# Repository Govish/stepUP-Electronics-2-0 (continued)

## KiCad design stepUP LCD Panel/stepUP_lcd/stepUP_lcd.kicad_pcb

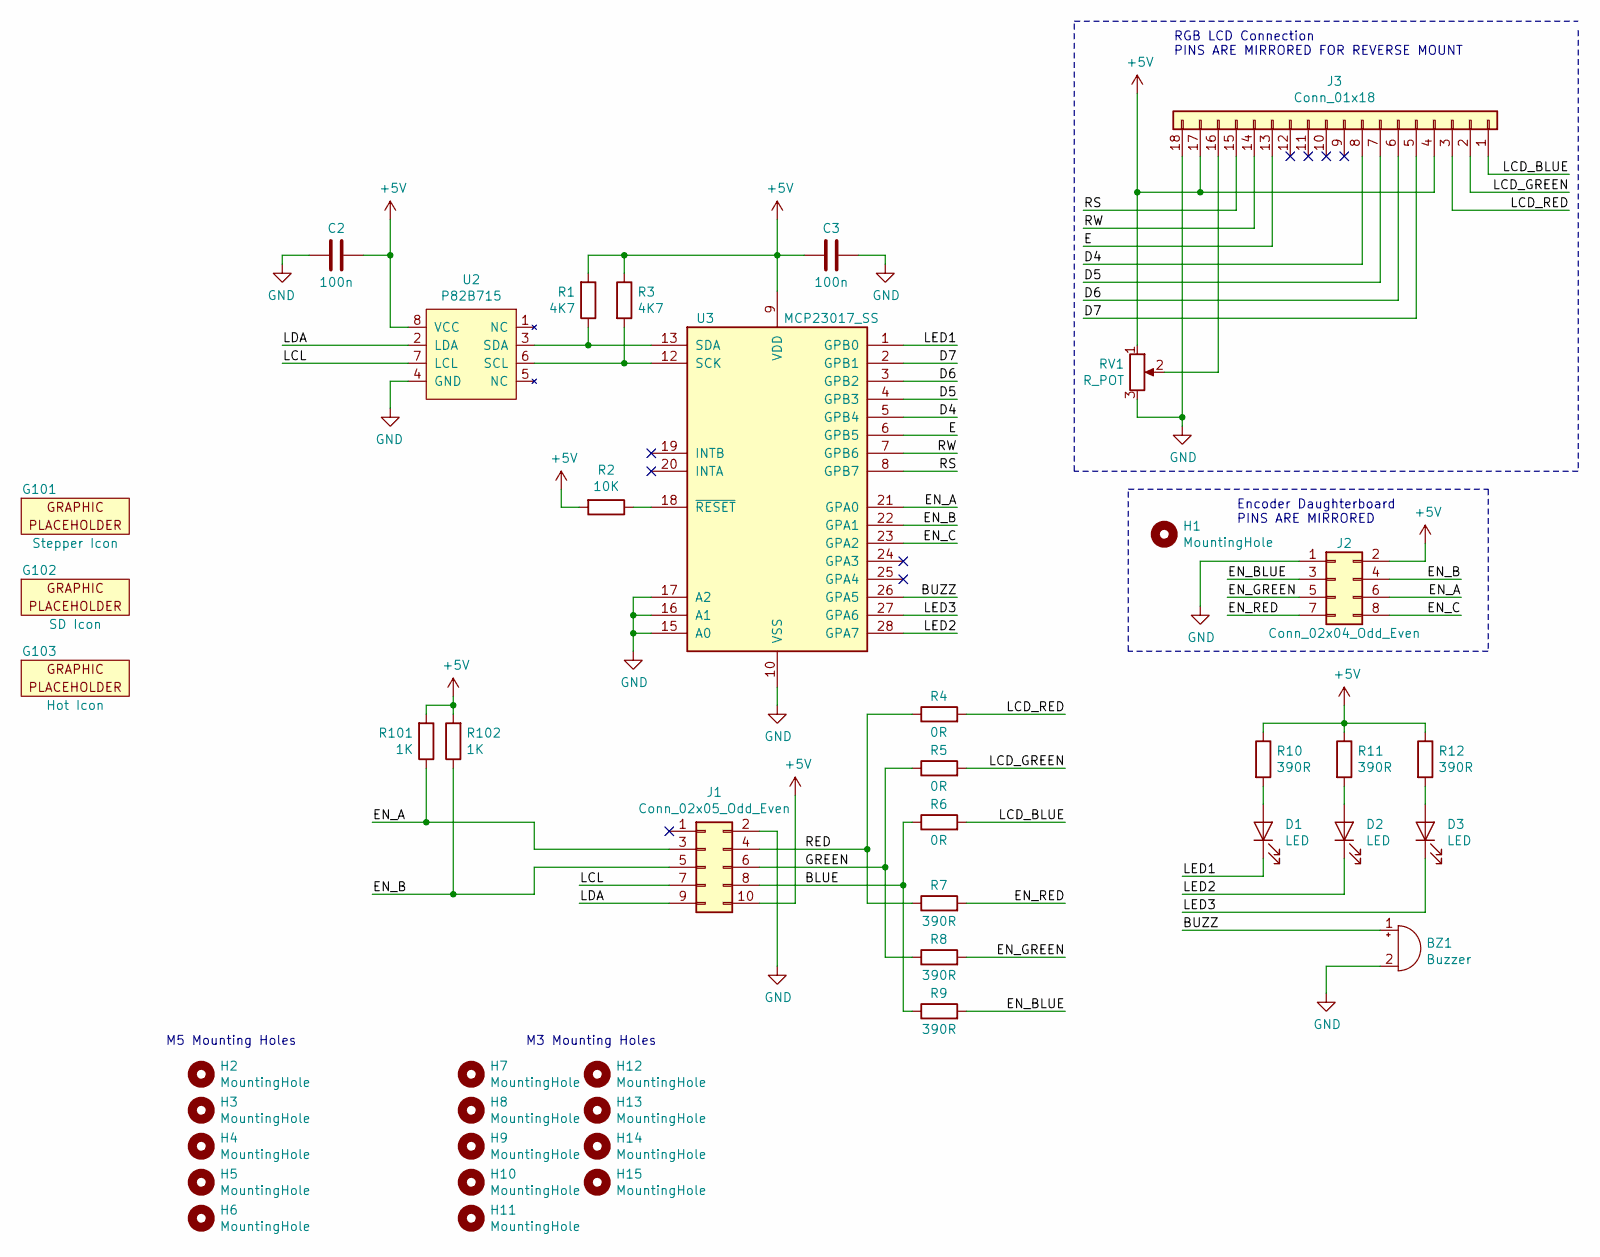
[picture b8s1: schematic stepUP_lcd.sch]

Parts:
BZ1: Buzzer; Buzzer_CUI_CPT9019S
C2, C3: 100n; C_0603_1608Metric_Pad1.05x0.95mm_HandSolder
D1, D2, D3: LED; LED_1206ReverseMount
G101: Stepper Icon; Icon_Stepper
G102: SD Icon; Icon_SD
G103: Hot Icon; Icon_Temp
H1: MountingHole; RGB_Encoder_Hole
H2, H3, H4, H5, H6: MountingHole; MountingHole_5.3mm_M5_Pad
H7, H8, H9, H10, H11, H12, H13, H14, H15: MountingHole; MountingHole_3.2mm_M3_Pad
J1: Conn_02x05_Odd_Even; PinHeader_2x05_P2.54mm_Shrouded
J2: Conn_02x04_Odd_Even; PinHeader_2x04_P2.54mm_Vertical_SMD
J3: Conn_01x18; PinHeader_1x18_P2.54mm_Vertical_SMD_Pin1Left
R1, R3: 4K7; R_0603_1608Metric_Pad1.05x0.95mm_HandSolder
R2: 10K; R_0603_1608Metric_Pad1.05x0.95mm_HandSolder
R4, R5, R6: 0R; R_0603_1608Metric_Pad1.05x0.95mm_HandSolder
R7, R8, R9, R10, R11, R12: 390R; R_0603_1608Metric_Pad1.05x0.95mm_HandSolder
R101, R102: 1K; R_0603_1608Metric_Pad1.05x0.95mm_HandSolder
RV1: R_POT; Potentiometer_Vishay_TS53YJ
U2: P82B715; SOIC-8_3.9x4.9mm_P1.27mm
U3: MCP23017_SS; SSOP-28_5.3x10.2mm_P0.65mm

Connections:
+5V: C2.2, C3.2, J1.10, J2.2, J3.4, J3.17, R1.2, R2.2, R3.1, R10.1, R11.1, R12.1, R101.2, R102.2, RV1.1, U2.8 (VCC), U3.9 (VDD)
/BLUE: J1.8, R6.1, R9.1
/BUZZ: BZ1.1 (-), U3.26 (GPA5)
/D4: J3.8, U3.5 (GPB4)
/D5: J3.7, U3.4 (GPB3)
/D6: J3.6, U3.3 (GPB2)
/D7: J3.5, U3.2 (GPB1)
/E: J3.13, U3.6 (GPB5)
/EN_A: J1.3, J2.6, R101.1, U3.21 (GPA0)
/EN_B: J1.5, J2.4, R102.1, U3.22 (GPA1)
/EN_BLUE: J2.3, R9.2
/EN_C: J2.8, U3.23 (GPA2)
/EN_GREEN: J2.5, R8.2
/EN_RED: J2.7, R7.2
/GREEN: J1.6, R5.1, R8.1
/LCD_BLUE: J3.1, R6.2
/LCD_GREEN: J3.2, R5.2
/LCD_RED: J3.3, R4.2
/LCL: J1.7, U2.7 (LCL)
/LDA: J1.9, U2.2 (LDA)
/LED1: D1.1 (K), U3.1 (GPB0)
/LED2: D2.1 (K), U3.28 (GPA7)
/LED3: D3.1 (K), U3.27 (GPA6)
/RED: J1.4, R4.1, R7.1
/RS: J3.15, U3.8 (GPB7)
/RW: J3.14, U3.7 (GPB6)
GND: BZ1.2 (+), C2.1, C3.1, J1.2, J2.1, J3.18, RV1.3, U2.4 (GND), U3.10 (VSS), U3.15 (A0), U3.16 (A1), U3.17 (A2)
unnamed: D1.2 (A), R10.2
unnamed: D2.2 (A), R11.2
unnamed: D3.2 (A), R12.2
unnamed: J3.16, RV1.2
unnamed: R1.1, U2.3 (SDA), U3.13 (SDA)
unnamed: R2.1, U3.18 (~RESET~)
unnamed: R3.2, U2.6 (SCL), U3.12 (SCK)

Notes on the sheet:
Encoder Daughterboard PINS ARE MIRRORED
RGB LCD Connection PINS ARE MIRRORED FOR REVERSE MOUNT
M5 Mounting Holes
M3 Mounting Holes

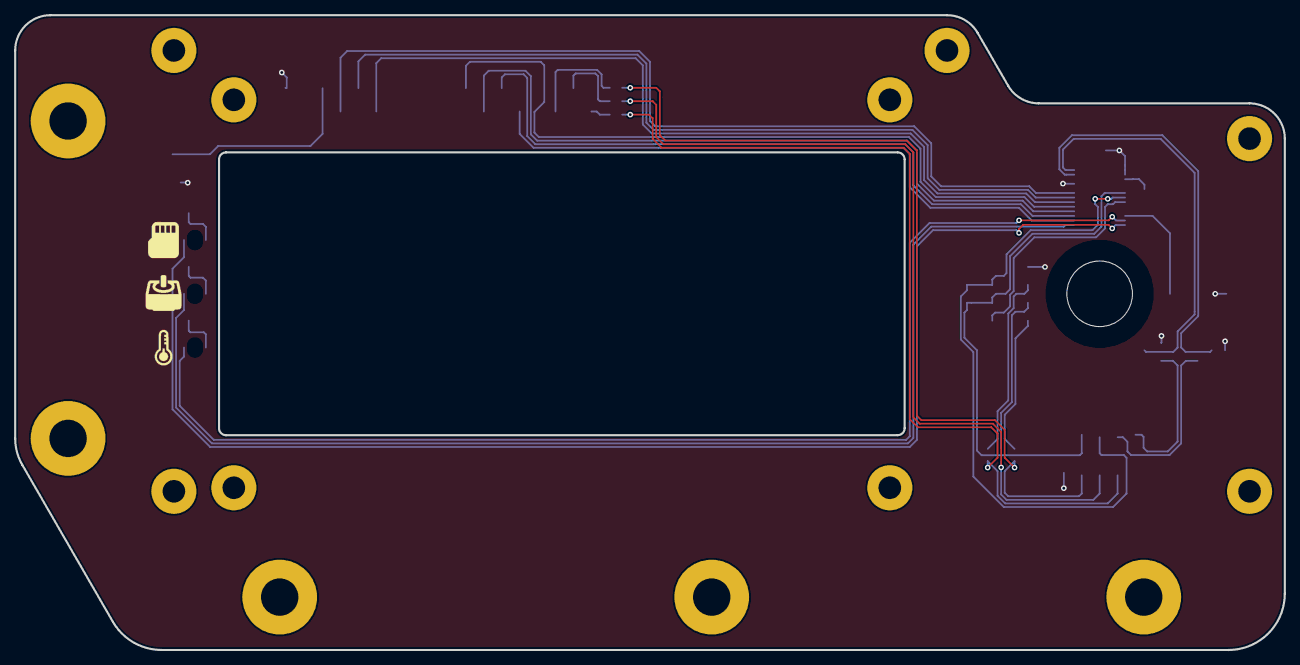
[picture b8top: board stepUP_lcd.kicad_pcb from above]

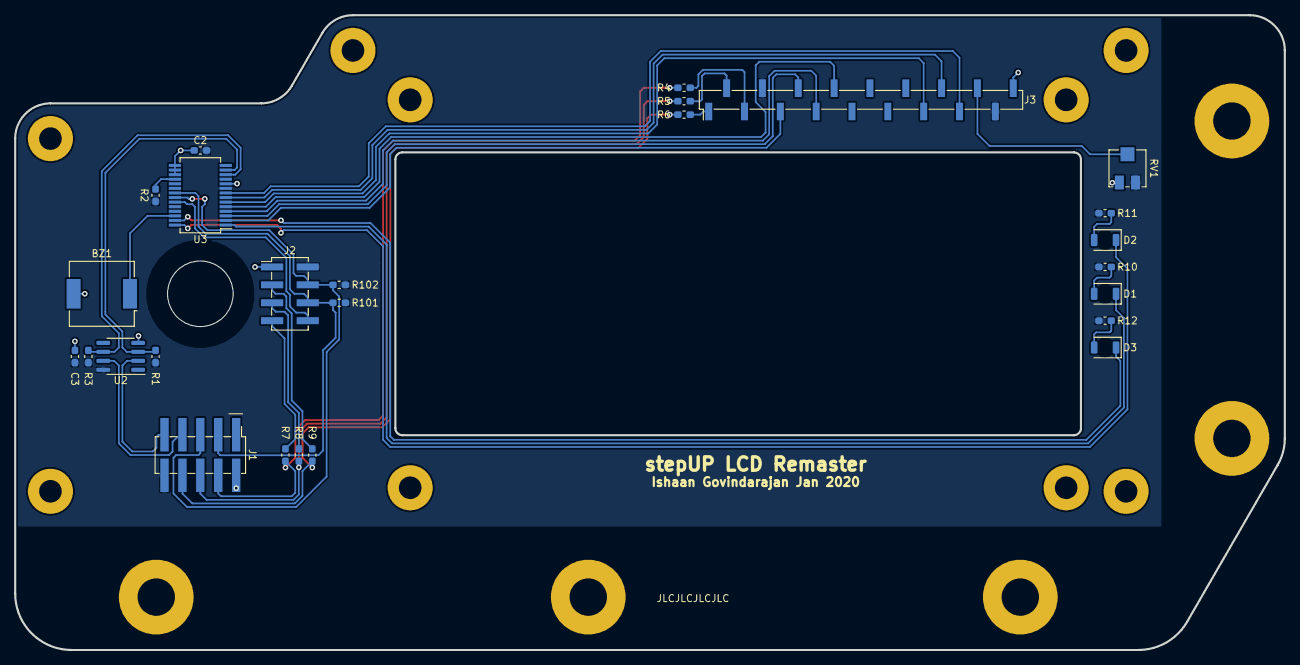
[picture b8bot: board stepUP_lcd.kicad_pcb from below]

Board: 2 copper layers, 180.0 x 90.0 mm, 44 parts (26 on the bottom side), 34 nets.

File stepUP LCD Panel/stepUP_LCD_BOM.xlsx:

stepUP LCD Bill of Materials
LAST UPDATED 9/25/2019
Reference Number | Package | Quantity | Price @Break | Total Price | Value | Manufacturer | Part Number | Supplier (DigiKey) P/N | Notes for Substitution | Qty on Hand
BZ1 | Nonstandard | 1 |  | 0 | -
C2, C3 | 0603 | 2 |  | 0 | 100n
D1 | 1206 Reverse Mount | 1 |  | 0 | Red
D2 | 1206 Reverse Mount | 1 |  | 0 | Yellow
D3 | 1206 Reverse Mount | 1 |  | 0 | Green
J1 | 02x05 SMD Pin Header | 1 |  | 0 | -
J2 | 02x04 SMD Pin Header | 1 |  | 0 | -
J3 | 01x18 SMD Pin Header | 1 |  | 0 | -
R1, R3 | 0603 | 2 |  | 0 | 4k7
R2 | 0603 | 1 |  | 0 | 10k
R4, R5, R6 | 0603 | 3 |  | 0 | 0R
R7, R8, R9, R10, R11, R12 | 0603 | 6 |  | 0 | 390R
R101, R102 | 0603 | 2 |  | 0 | 1k
RV1 | Nonstandard | 1 |  | 0 | R_POT
U2 | SOIC-8 (3.9x4.9_P1.27) | 1 |  | 0 | P82B715
U3 | SSOP-28 (5.3x10.2_P0.65) | 1 |  | 0 | MCP23017

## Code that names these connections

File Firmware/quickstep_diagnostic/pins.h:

#ifndef PINS_H
#define PINS_H

//========== MISC PINS =========
#define PS_ON 2
#define VMOT_GOOD 17
#define SD_CD A3

#define LED_RED 10
#define LED_GREEN 11
#define LED_BLUE 12
//==============================

//=========== SCHMITT TRIGGER INPUTS ========
#define ENC_A 46
#define ENC_B 49
#define X_STOP 44
#define Y_STOP 48
#define Z_STOP 47
#define RUNOUT 45

//======== THERMAL CONTROL ========
#define EXT_THERM A1
#define BED_THERM A0

#define PRINT_FAN 7
#define EXTRUDER 8
#define HEATED_BED 9
//=================================

//=============== STEPPER DRIVERS =============
#define X_STEP 35
#define X_DIR 34
#define X_EN 33
#define X_CS 32
#define X_DIAG0 36
#define X_DIAG1 37

#define Y_STEP 41
#define Y_DIR 40
#define Y_EN 39
#define Y_CS 38
#define Y_DIAG0 42
#define Y_DIAG1 43

#define Z_STEP 24
#define Z_DIR 25
#define Z_EN 22
#define Z_CS 23
#define Z_DIAG0 20
#define Z_DIAG1 21

#define E_STEP 28
#define E_DIR 29
#define E_EN 26
#define E_CS 27
#define E_DIAG0 30
#define E_DIAG1 31
//==============================================

inline void OUTLOW(int pin) {
  pinMode(pin, OUTPUT);
  digitalWrite(pin, LOW);
}
inline void OUTHIGH(int pin) {
  pinMode(pin, OUTPUT);
  digitalWrite(pin, HIGH);
}
inline void IN(int pin) {pinMode(pin, INPUT);}
inline void INPULL(int pin) {pinMode(pin, INPUT_PULLUP);}
inline void SETHIGH(int pin) {digitalWrite(pin, HIGH);}
inline void SETLOW(int pin) {digitalWrite(pin, LOW);}
inline bool READ(int pin) {return digitalRead(pin);}
inline void TOGGLE(int pin) {digitalWrite(pin, !READ(pin));}

void pins_init() {
  //==== general pins =====
  OUTLOW(PS_ON);
  OUTLOW(LED_RED);
  OUTLOW(LED_GREEN);
  OUTLOW(LED_BLUE);
  IN(VMOT_GOOD);
  INPULL(SD_CD);

  //====== schimtt inputs =====
  IN(ENC_A);
  IN(ENC_B);
  IN(X_STOP);
  IN(Y_STOP);
  IN(Z_STOP);
  IN(RUNOUT);

  //====== thermal control ======
  IN(EXT_THERM);
  IN(BED_THERM);
  OUTLOW(PRINT_FAN);
  OUTLOW(EXTRUDER);
  OUTLOW(HEATED_BED);

  //======= drivers ========
  OUTLOW(X_STEP);
  OUTLOW(X_DIR);
  OUTHIGH(X_EN);
  OUTHIGH(X_CS);

  OUTLOW(Y_STEP);
  OUTLOW(Y_DIR);
  OUTHIGH(Y_EN);
  OUTHIGH(Y_CS);

  OUTLOW(Z_STEP);
  OUTLOW(Z_DIR);
  OUTHIGH(Z_EN);
  OUTHIGH(Z_CS);

  OUTLOW(E_STEP);
  OUTLOW(E_DIR);
  OUTHIGH(E_EN);
  OUTHIGH(E_CS);

  OUTLOW(X_DIAG0);
  OUTLOW(X_DIAG1);
  OUTLOW(Y_DIAG0);
  OUTLOW(Y_DIAG1);
  OUTLOW(Z_DIAG0);
  OUTLOW(Z_DIAG1);
  OUTLOW(E_DIAG0);
  OUTLOW(E_DIAG1);
}

void step_motors() {
  SETHIGH(X_STEP);
  SETHIGH(Y_STEP);
  SETHIGH(Z_STEP);
  SETHIGH(E_STEP);
  delayMicroseconds(500);
  SETLOW(X_STEP);
  SETLOW(Y_STEP);
  SETLOW(Z_STEP);
  SETLOW(E_STEP);
  delayMicroseconds(500);
}


#endif

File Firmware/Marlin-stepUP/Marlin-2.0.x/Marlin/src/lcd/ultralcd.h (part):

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
  #ifdef EN_C
    #ifdef INVERT_BUTTON_CLICKED
      #define BUTTON_CLICK() ((~buttons & EN_C) || RRK(EN_KEYPAD_MIDDLE))
    #else
      #define BUTTON_CLICK() ((buttons & EN_C) || RRK(EN_KEYPAD_MIDDLE))
    #endif
  #else
    #define BUTTON_CLICK() RRK(EN_KEYPAD_MIDDLE)
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  #define BLEN_A 0
  #define BLEN_B 1

  #define EN_A _BV(BLEN_A)
  #define EN_B _BV(BLEN_B)

  #define BUTTON_PRESSED(BN) !READ(BTN_## BN)

  #if BUTTON_EXISTS(ENC) || ENABLED(TOUCH_BUTTONS)
    #define BLEN_C 2
    #define EN_C _BV(BLEN_C)
  #endif

  #if ENABLED(LCD_I2C_VIKI)

    #include <LiquidTWI2.h>

    #define B_I2C_BTN_OFFSET 3 // (the first three bit positions reserved for EN_A, EN_B, EN_C)

    // button and encoder bit positions within 'buttons'
    #define B_LE (BUTTON_LEFT   << B_I2C_BTN_OFFSET)      // The remaining normalized buttons are all read via I2C
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    #define B_RI (BUTTON_RIGHT  << B_I2C_BTN_OFFSET)

    #if BUTTON_EXISTS(ENC)                                // The pause/stop/restart button is connected to BTN_ENC when used
      #define B_ST (EN_C)                                 // Map the pause/stop/resume button into its normalized functional name
      #define BUTTON_CLICK() (buttons & (B_MI|B_RI|B_ST)) // Pause/stop also acts as click until a proper pause/stop is implemented.
    #else
      #define BUTTON_CLICK() (buttons & (B_MI|B_RI))
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
    #if !BUTTON_EXISTS(ENC) // Use I2C if not directly connected to a pin

      #define B_I2C_BTN_OFFSET 3 // (the first three bit positions reserved for EN_A, EN_B, EN_C)

      #define B_MI (PANELOLU2_ENCODER_C << B_I2C_BTN_OFFSET) // requires LiquidTWI2 library v1.2.3 or later
      #ifdef INVERT_BUTTON_CLICK
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
#ifndef BUTTON_CLICK
  #ifdef EN_C
    #define BUTTON_CLICK() (buttons & EN_C)
  #else
    #define BUTTON_CLICK() false
  #endif
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  }

  #if HAS_BUZZER
    static void buzz(const long duration, const uint16_t freq);
  #endif

  #if ENABLED(LCD_HAS_STATUS_INDICATORS)
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
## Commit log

2020-06-04 Reuploading Entire Repo
2020-06-16 Removing ESP3D v3, Fixing display throtting issues for Marlin
2020-06-19 Messing around with direct SD-MMC upload; hardware changes required and messing around with ESP3D
2020-07-05 Adding Quickstep diagnostic test, and messing around with Trinamic driver settings
2020-07-09 Changes for V6 Hotend, messing around with cold pull script, minor bugfix for unload
2020-07-18 Removing filament unload from LCD Menu, swapping to classic jerk for extruder jerk control
2020-12-12 Bump ini from 1.3.5 to 1.3.8 in /Firmware/ESP3D-2.1 stepUP/embedded
    Bumps [ini](https://github.com/isaacs/ini) from 1.3.5 to 1.3.8.
    - [Release notes](https://github.com/isaacs/ini/releases)
    - [Commits](https://github.com/isaacs/ini/compare/v1.3.5...v1.3.8)
2021-03-31 Bump y18n from 3.2.1 to 3.2.2 in /Firmware/ESP3D-2.1 stepUP/embedded
    Bumps [y18n](https://github.com/yargs/y18n) from 3.2.1 to 3.2.2.
    - [Release notes](https://github.com/yargs/y18n/releases)
    - [Changelog](https://github.com/yargs/y18n/blob/master/CHANGELOG.md)
    - [Commits](https://github.com/yargs/y18n/commits)
2021-05-11 Bump hosted-git-info in /Firmware/ESP3D-2.1 stepUP/embedded
    Bumps [hosted-git-info](https://github.com/npm/hosted-git-info) from 2.8.4 to 2.8.9.
    - [Release notes](https://github.com/npm/hosted-git-info/releases)
    - [Changelog](https://github.com/npm/hosted-git-info/blob/v2.8.9/CHANGELOG.md)
    - [Commits](https://github.com/npm/hosted-git-info/compare/v2.8.4...v2.8.9)
2021-08-12 Bump path-parse in /Firmware/ESP3D-2.1 stepUP/embedded
    Bumps [path-parse](https://github.com/jbgutierrez/path-parse) from 1.0.6 to 1.0.7.
    - [Release notes](https://github.com/jbgutierrez/path-parse/releases)
    - [Commits](https://github.com/jbgutierrez/path-parse/commits/v1.0.7)
    ---
    updated-dependencies:
    - dependency-name: path-parse
2022-06-27 Bump copy-props in /Firmware/ESP3D-2.1 stepUP/embedded
    Bumps [copy-props](https://github.com/gulpjs/copy-props) from 2.0.4 to 2.0.5.
    - [Release notes](https://github.com/gulpjs/copy-props/releases)
    - [Changelog](https://github.com/gulpjs/copy-props/blob/master/CHANGELOG.md)
    - [Commits](https://github.com/gulpjs/copy-props/compare/2.0.4...2.0.5)
    ---
    updated-dependencies:
2022-12-06 Bump decode-uri-component in /Firmware/ESP3D-2.1 stepUP/embedded
    Bumps [decode-uri-component](https://github.com/SamVerschueren/decode-uri-component) from 0.2.0 to 0.2.2.
    - [Release notes](https://github.com/SamVerschueren/decode-uri-component/releases)
    - [Commits](https://github.com/SamVerschueren/decode-uri-component/compare/v0.2.0...v0.2.2)
    ---
    updated-dependencies:
    - dependency-name: decode-uri-component
2024-07-20 Including copy of LiquidTWI2 and some minor Marlin changes to get stepUP working again
